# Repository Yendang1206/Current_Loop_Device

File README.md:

# Digital Current Loop Device for Frequency Converters
This repository contains the design and implementation details of a digital current loop device for frequency converters, developed as part of a thesis project. This device serves as an intermediate unit between a motor and a frequency converter, featuring advanced functionalities such as fast and slow increments or decrements for user-friendly control.
## Overview
The digital current loop device converts digital inputs—representing torque (0–50 Nm) and speed (0–3000 rpm)—into 0–20 mA analog current loops. This project integrates hardware and software to achieve precise control, accurate signal processing, and robust performance in noisy environments.
## Key Features
+ Converts torque and speed inputs from a rotary encoder into 0–20 mA current loop outputs.
+ Displays real-time input values on an LCD I2C screen.
+ Offers convenient fast/slow increment and decrement control.
+ Incorporates grounding, shielding, and paired signal wiring to enhance signal stability.
## The work methods
The work methods for this project were split into three main stages: 
 + circuit design, simulation and prototyping,
 + developing an Arduino software program,
 + manufacturing the physical Printed Circuit Boards (PCB).
## Results
Demonstrated positive correlation between torque and speed inputs with the corresponding current loop values (0–20 mA).
Achieved consistent performance between breadboard prototypes and integrated PCB systems.
Eliminated capacitive crosstalk and frequency interference using proper grounding, shielding, and CAT6 cable pairing.
## How to use
1. Connect the device between the motor and the frequency converter.
2. Adjust torque and speed inputs using the rotary encoder.
3. Monitor real-time input values on the LCD I2C display.
4. Verify current loop outputs using multimeters for accuracy.
## Future recommendations
Conduct EMC testing to further enhance noise immunity and long-term stability.

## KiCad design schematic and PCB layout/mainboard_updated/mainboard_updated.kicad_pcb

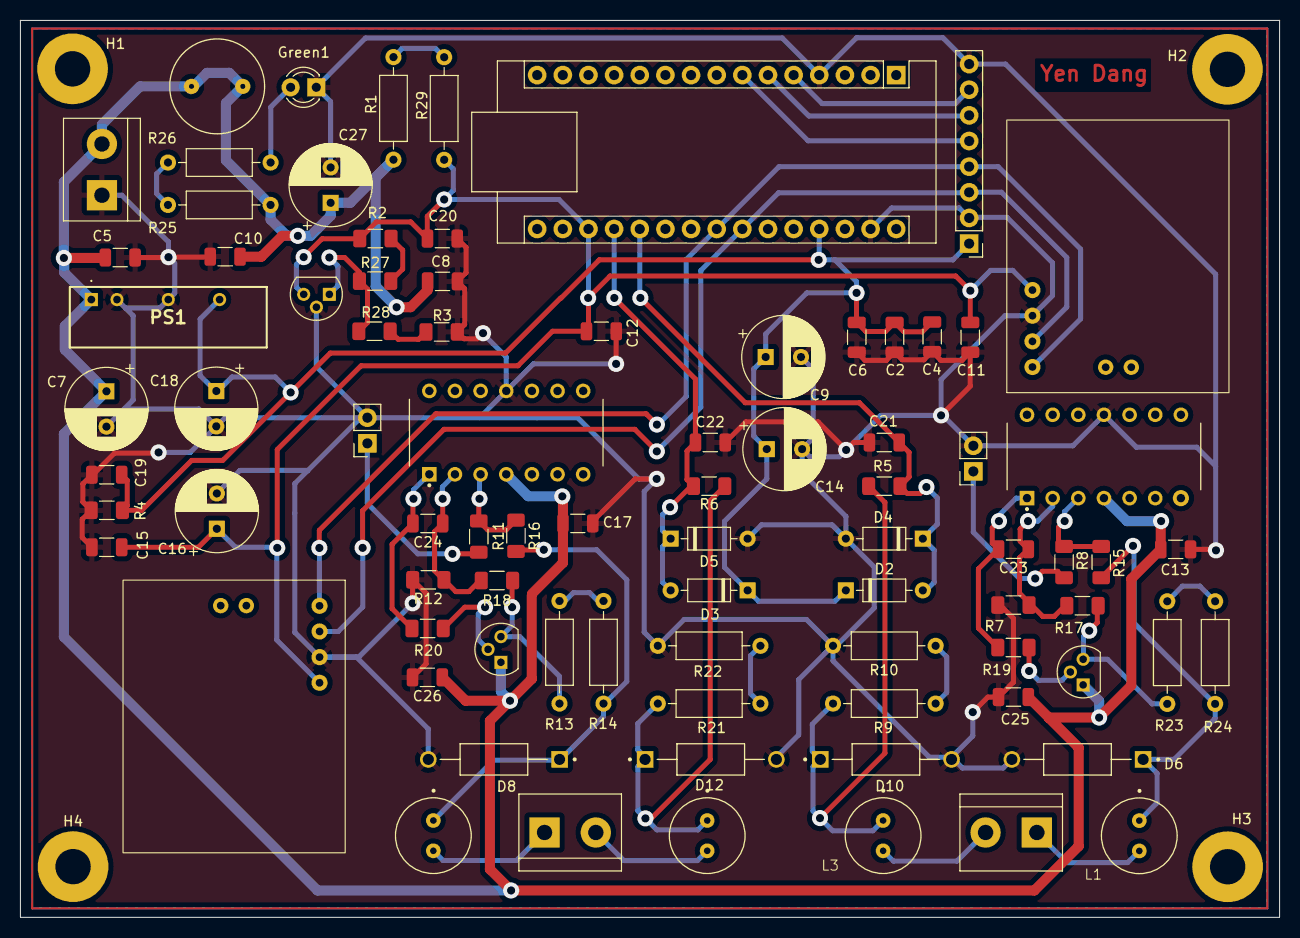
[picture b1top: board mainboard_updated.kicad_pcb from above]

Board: 2 copper layers, 124.7 x 88.8 mm, 87 parts (0 on the bottom side), 41 nets.

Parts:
 Green1: GreenLED; LED
A1: Arduino_Nano_v3.x; Arduino_Nano
BC547_1, BC547_2: BC547_TO92_0.1A; TO-92
C2, C4, C5, C6, C8, C10, C11, C12, C13, C15, C17, C19, C20, C21, C22, C23, C24, C25, C26: 100NF_50V_CER; C1206
C7, C9, C14, C16, C18, C27: 100UF_50V_ELE; C_P_3_5_8
D2, D3, D4, D5: 1N4148; D_DO-35_SOD27_P7.62mm_Horizontal
D6, D8, D10, D12: P6KE43CA; DIOAD1300W80L670D310
F1: TR5; FUSE_TR5
H1, H2, H3, H4: MountingHole_Pad_MP; MountingHole_3.5mm_Pad
L1, L2, L3, L4: Coil3; Coil3_100uH
PS1: AM2D-2405SZ; AM2D2405SZ
R1, R29: 910R; R3_5W
R2, R3, R5, R6: 10k; 1206
R4: 470R; 1206
R7, R8, R11, R12, R15, R16, R17, R18: 150k; 1206
R9, R13, R21, R23: 100R; R3_5W
R10, R14, R22, R24: 150R; R3_5W
R19, R20: 100R; 1206
R25, R26: 2.2k; R3_5W
R27: 0R; 1206
R28: 150R; 1206
ROW_VERT/1X1: ROW_VERT_1X8; ROW_VERT_1x8
SOCKET/1X1, SOCKET/1X2: SOCKET_1X2; SOCKET_1x2
TL431CLP1: TL431CLP_TO92; TO-92
TM_BLOCK/2P1, TM_BLOCK/2P2, TM_BLOCK/2P3: TM_BLOCK_2P
U1, U2: DFR0552
U3, U4: LM324NE4; DIP825W47P254L1917H533Q14

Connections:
5V: A1.27 (+5V), C2.1, C4.1, C6.1, C9.1, C14.1, C18.1, C19.1, D2.1 (K), D3.1 (K), PS1.6 (+V_OUT), R4.2, ROW_VERT/1X1.1
+24V: BC547_1.1 (C), BC547_2.1 (C), C5.1, C7.1, C8.1, C10.1, C13.1, C17.1, C25.1, C26.1, C27.1, F1.1, F1.2, PS1.1 (+Vin), R1.1, R25.2, TM_BLOCK/2P1.2, U3.4, U4.4
A0: A1.19 (A0), C22.1, D3.2 (A), D5.1 (K), R6.2
A1: A1.20 (A1), C21.1, D2.2 (A), D4.1 (K), R5.2
EncoderA: A1.5 (D2), ROW_VERT/1X1.7
EncoderB: A1.6 (D3), ROW_VERT/1X1.6
GND: Green1.1 (K), A1.4 (GND), A1.29 (GND), C2.2, C4.2, C5.2, C6.2, C7.2, C8.2, C9.2, C10.2, C11.1, C12.2, C13.2, C14.2, C15.1, C16.2, C17.2, C18.2, C19.2, C20.2, C21.2, C22.2, C25.2, C26.2, C27.2, D4.2 (A), D5.2 (A), D6.A, D8.A, D10.A, D12.A, PS1.2 (-Vin), PS1.4 (-V_OUT), R3.1, R4.1, R7.1, R10.1, R12.1, R22.1, ROW_VERT/1X1.2, ROW_VERT/1X1.8, SOCKET/1X1.2, SOCKET/1X2.2, TL431CLP1.2 (A), TM_BLOCK/2P1.1, U1.2 (GND), U2.2 (GND), U3.11, U4.11
unnamed: Green1.2 (A), R26.1
unnamed: BC547_1.2 (B), R19.2
unnamed: BC547_1.3 (E), R17.2, R23.2
unnamed: BC547_2.2 (B), R20.2
unnamed: BC547_2.3 (E), R13.2, R18.2
unnamed: C23.1, R7.2, R17.1, U3.2
unnamed: C23.2, R19.1, U3.1
unnamed: C24.1, R12.2, R18.1, U4.2
unnamed: C24.2, R20.1, U4.1
unnamed: D6.C, L1.1, R15.1, R24.1
unnamed: D8.C, L2.1, R14.1, R16.1
unnamed: D10.C, L3.1, R5.1, R9.2
unnamed: D12.C, L4.1, R6.1, R21.2
unnamed: R1.2, R29.1
unnamed: R2.1, R27.2
unnamed: R9.1, R10.2
unnamed: R11.2, R16.2, U4.3
unnamed: R13.1, R14.2
unnamed: R8.2, R15.2, U3.3
unnamed: R21.1, R22.2
unnamed: R23.1, R24.2
unnamed: R25.1, R26.2
unnamed: R3.2, R28.1
unnamed: R27.1, R28.2, TL431CLP1.1 (REF)
unnamed: L1.2, TM_BLOCK/2P2.1
unnamed: L3.2, TM_BLOCK/2P2.2
unnamed: L2.2, TM_BLOCK/2P3.1
unnamed: L4.2, TM_BLOCK/2P3.2
SCL: A1.24 (A5), ROW_VERT/1X1.3, U1.3 (SCL), U2.3 (SCL)
SDA: A1.23 (A4), ROW_VERT/1X1.4, U1.4 (SDA), U2.4 (SDA)
SW1: A1.7 (D4), ROW_VERT/1X1.5
V_DAC1: R8.1, SOCKET/1X1.1
V_DAC2: R11.1, SOCKET/1X2.1
Vref: A1.18 (AREF), C11.2, C12.1, C15.2, C16.1, C20.1, R2.2, R29.2, TL431CLP1.3 (K), U1.1 (VCC), U2.1 (VCC)

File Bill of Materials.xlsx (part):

|  | Bill of Materials |  |  |  |  |  |  | Note
Supplier | No. | Description | Order Code | Quantity | Unit Price (incl. VAT) (EUR) | Price (incl. VAT) (EUR) |  |  | Reference | Supplier
Elfa | 1 | Capacitor 100NF_50V_CER | 165-77-688 | 23 | 0.37469999999999998 | 8.6181000000000001 |  |  | C1-C6, C8, C10-C13, C15, C17, C19-C26,C6, C8, C10, C12 | https://www.elfadistrelec.fi/fi/keraaminen-kondensaattori-10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
Elfa | 2 | Capacitor 100UF_50V_ELE | 300-92-030 | 7 | 0.18720000000000001 | 1.3104 |  |  | C7, C9, C14, C16, C18, C3, C27 | https://www.elfadistrelec.fi/fi/radiaalinen-elektrolyyttikon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
Elfa | 3 | ROW_VERT_1X8 | 43-70-219 | 1 | 1.18 | 1.18 |  |  | ROW_VERT/1X1, ROW_VERT/1X2 | https://www.elfadistrelec.fi/fi/piikkirima-uros-1a-kontaktie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
Elfa | 4 | LCD holder for the small metal box | 175-57-723 | 1 | 21.06 | 21.06 |  |  | LCD holder for the small metal box | https://www.elfadistrelec.fi/fi/lcd-naeytoen-etukehys-displa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
Elfa | 5 | Cable CAT6 1.5m | 302-29-454 | 1 | 5.99 | 5.99 |  |  | Cable CAT 6 1.5m | https://www.elfadistrelec.fi/fi/kytkentaekaapeli-rj45-urosli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
Elfa | 6 | EMC sleeve seal | 301-40-348 | 5 | 8.7100000000000009 | 43.550000000000004 |  |  | EMC sleeve seal | https://www.elfadistrelec.fi/fi/emc-holkkitiiviste-10mm-m16-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
Farnell | 7 | GreenLED | 3796272 | 1 | 0.28148000000000001 | 0.28148000000000001 |  |  | Green1 | https://fi.farnell.com/en-FI/multicomp-pro/mp008246/led-gree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
Farnell | 8 | Arduino_Nano_v3.x | 1848691 | 1 | 26.077200000000001 | 26.077200000000001 |  |  | A1 | https://fi.farnell.com/arduino/a000005/arduino-nano-evaluati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
Farnell | 9 | BC547_TO92_0.1A | 1017673 | 2 | 0.155 | 0.31 |  |  | BC547_1, BC547_2 | https://fi.farnell.com/en-FI/onsemi/bc547bg/transistor-npn-4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
Farnell | 10 | 1N4148 | 9843680 | 4 | 1.9096000000000002E-2 | 7.6384000000000007E-2 |  |  | D2-D5 | https://fi.farnell.com/en-FI/multicomp-pro/1n4148/diode-ultr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
Farnell | 11 | P6KE43CA/P6KEG39CA | 3226355 | 5 | 0.33604000000000001 | 1.6802000000000001 |  |  | D6-D13,D1 | https://fi.farnell.com/en-FI/multicomp-pro/p6keg39ca/tvs-dio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
Farnell | 12 | Resistor 1.8k SMD (replace by 2 TH resistors of 910R) | Removed |  |  | 0 |  |  |  | https://fi.farnell.com/en-FI/panasonic/era8aeb182v/res-1k8-0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
Farnell | 13 | Resistor 10k SMD (update footprint from 2010 to 1206) | 1469655 | 12 | 0.42160000000000003 | 5.0592000000000006 |  |  | R2, R3, R5, R6, R1-R8 | https://fi.farnell.com/en-FI/vishay/crcw120610k0jnea/res-10k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
Farnell | 14 | Resistor 470R SMD (update footprint from 0805 to 1206) | 2671182 | 1 | 2.3311999999999999E-2 | 2.3311999999999999E-2 |  |  | R4 | https://fi.farnell.com/en-FI/walsin/wr12x471-jtl/res-470r-5-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
Farnell | 15 | Resistor 150k SMD | 1841797 | 8 | 0.36207999999999996 | 2.8966399999999997 |  |  | R7, R8, R11, R12, R15-R18 | https://fi.farnell.com/en-FI/panasonic/era8aeb154v/res-150k-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
Farnell | 16 | Resistor 100R SMD | 3392888 | 2 | 5.0963999999999995E-2 | 0.10192799999999999 |  |  | R19, R20 | https://fi.farnell.com/en-FI/multicomp-pro/mp003694/res-100r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
Farnell | 17 | Resistor 100R TH (change from 400mW to 600mW) | 9463909 | 4 | 0.18103999999999998 | 0.72415999999999991 |  |  | R9, R13, R21, R23 | https://fi.farnell.com/vishay/mrs25000c1000fct00/res-100r-1-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
Farnell | 18 | Resistor 150R TH (change from 250mW to 600mW) | 9464638 | 4 | 0.17731999999999998 | 0.70927999999999991 |  |  | R10, R14, R22, R24 | https://fi.farnell.com/vishay/mrs25000c1500fct00/res-150r-1-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
Farnell | 19 | Resistor 2.2k TH (change from 2W to 600mW) | 9466711 | 2 | 0.18103999999999998 | 0.36207999999999996 |  |  | R25, R26 | https://fi.farnell.com/vishay/mrs25000c2201fct00/res-2k2-1-6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
Farnell | 20 | SOCKET_1X8 (replace for ROW_VERTICAL HEADER at mainboard) | 2802333 | 1 | 1.08128 | 1.08128 |  |  | Replace for ROW_VERTICAL PIN HEADER at mainboard | https://fi.farnell.com/en-FI/mcm/83-15410/1-x-8-position-fem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
Farnell | 21 | SOCKET*2_1X10 | 1593464 | 1 | 0.52700000000000002 | 0.52700000000000002 |  |  | SOCKET/1X1, SOCKET/1X2 | https://fi.farnell.com/multicomp/2212s-10sg-85/socket-pcb-1-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
Farnell | 22 | TL431CLP_TO92 | 9756450 | 1 | 0.87791999999999992 | 0.87791999999999992 |  |  | TL431CLP1 | https://fi.farnell.com/stmicroelectronics/tl431acz/voltage-r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
Farnell | 23 | TM_BLOCK_2P | 3882652 | 4 | 2.3559999999999999 | 9.4239999999999995 |  |  | TM_BLOCK/2P1-TM_BLOCK/2P3 | https://fi.farnell.com/camdenboss/ctb0308-2/terminal-block-w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
Farnell | 24 | DFR0552 | 3517945 | 2 | 6.2247999999999992 | 12.449599999999998 |  |  | U1, U2 | https://fi.farnell.com/dfrobot/dfr0552/i2c-12-bit-dac-module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
Farnell | 25 | Capacitor 10NF_50V_CER SMD (update footprint from 0402 to 1206) | 2906003 | 3 | 0.13267999999999999 | 0.39803999999999995 |  |  | C1, C2, C4 | https://fi.farnell.com/kemet/c0402c103j5racauto/cap-0-01-f-5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
Farnell | 26 | ROW_VERT_1X4 | 2852586 | 1 | 0.2666 | 0.2666 |  |  | ROW_VERT/1X1 | https://fi.farnell.com/en-FI/multicomp/mc-hvt1-s04-g/connect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
Farnell | 27 | TVS Varistor | 1004301 | 1 | 1.1160000000000001 | 1.1160000000000001 |  |  | RV1 | https://fi.farnell.com/epcos/b72220s0500k101/varistor-27-0j-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
Farnell | 28 | Filter B82725S2103N003 | 3580935 | 1 | 11.209599999999998 | 11.209599999999998 |  |  | FL1 | https://fi.farnell.com/epcos/b82725s2103n003/power-line-chok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
Farnell | 29 | Toroidal Inductor, Vertical, 100uH | 2215971 | 1 | 6.6464000000000008 | 6.6464000000000008 |  |  | L1 | https://fi.farnell.com/pulse-electronics/pe-92112knl/inducto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
Farnell | 30 | Capacitor 10nF TH | 2576736 | 1 | 0.34720000000000001 | 0.34720000000000001 |  |  | C2 (filter circuit) | https://fi.farnell.com/walsin/yv1ac103m140d20c7b/cap-0-01-f-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
Farnell | 31 | Capacitor 2200pF TH | 2507755 | 2 | 0.59519999999999995 | 1.1903999999999999 |  |  | C1 and C3 (filter circuit) | https://fi.farnell.com/vishay/vy1222m47y5uq6uv0/cap-2200pf-2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
Farnell | 32 | Encoder's knob | Removed |  |  | 0 |  |  | Encoder's knob | https://fi.farnell.com/alcoswitch-te-connectivity/pka50b1-4/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
Farnell | 33 | Screw 3.5x12mm | 2400762 | 12 | 2.3188 | 27.825600000000001 |  |  | Screw 3.5x12mm | https://fi.farnell.com/deltron-components/000-035-004/std-sc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
Farnell | 34 | Heat Sink, 60 °C/W, TO-92, 15.29 mm, 18.29 mm | 2822615 | 2 | 6.2619999999999996 | 12.523999999999999 |  |  | Heatsink for TO-92 transistor | https://fi.farnell.com/en-FI/aavid-thermalloy/575200b00000g/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
Farnell | 35 | Resistor 910R TH | 9470581 | 2 | 0.1736 | 0.34720000000000001 |  |  | R1, R29 | https://fi.farnell.com/en-FI/vishay/mrs25000c9100fct00/res-9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
Farnell | 36 | Resistor 0R SMD | 9240276 | 1 | 3.7199999999999997E-2 | 3.7199999999999997E-2 |  |  | R27 | https://fi.farnell.com/en-FI/yageo/rc1206jr-070rl/res-0r0-5-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
Farnell | 37 | Resistor 150R SMD | 2531869 | 1 | 0.23808000000000001 | 0.23808000000000001 |  |  | R28 | https://fi.farnell.com/en-FI/te-connectivity/crgs1206j150r/r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
Farnell | 38 | TM_BLOCK_3P | 3882664 | 1 | 3.4471999999999996 | 3.4471999999999996 |  |  | TM_BLOCK_3P (filter circuit) | https://fi.farnell.com/camdenboss/ctb0308-3/terminal-block-w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
Partco | 39 | LCD I2C | LCD 2X16-I2C | 1 | 12.8 | 12.8 |  |  | LCD I2C | https://www.partco.fi/fi/naeytoet/lcd-naeytoet/20158-lcd-2x1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
Partco | 40 | Heatsinks for power chip (2pcs/1bag) | RPI-02893 | 1 | 4.8 | 4.8 |  |  | Heatsinks for power chip | https://www.partco.fi/fi/laemmoenhallinta/jaeaehdytyselement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
Starelec | 41 | TR5-K | 170-00181 | 1 | 0.55000000000000004 | 0.55000000000000004 |  |  | F1 | https://www.starelec.fi/product_info.php?cPath=66_335_3295&p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
Starelec | 42 | COIL3-100UH (mainboard) | COIL3-100UH | 4 | 0.5 | 2 |  |  | L1-L4 | https://www.starelec.fi/product_info.php?products_id=21043
Starelec | 43 | AM2D-2405SZ | DC2WS-2405S | 1 | 7.06 | 7.06 |  |  | PS1 | https://www.starelec.fi/product_info.php?cPath=72_155_2374&p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
Starelec | 44 | LM324NE4 | LM324N | 2 | 0.74 | 1.48 |  |  | U3, U4 | https://www.starelec.fi/product_info.php?products_id=112
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
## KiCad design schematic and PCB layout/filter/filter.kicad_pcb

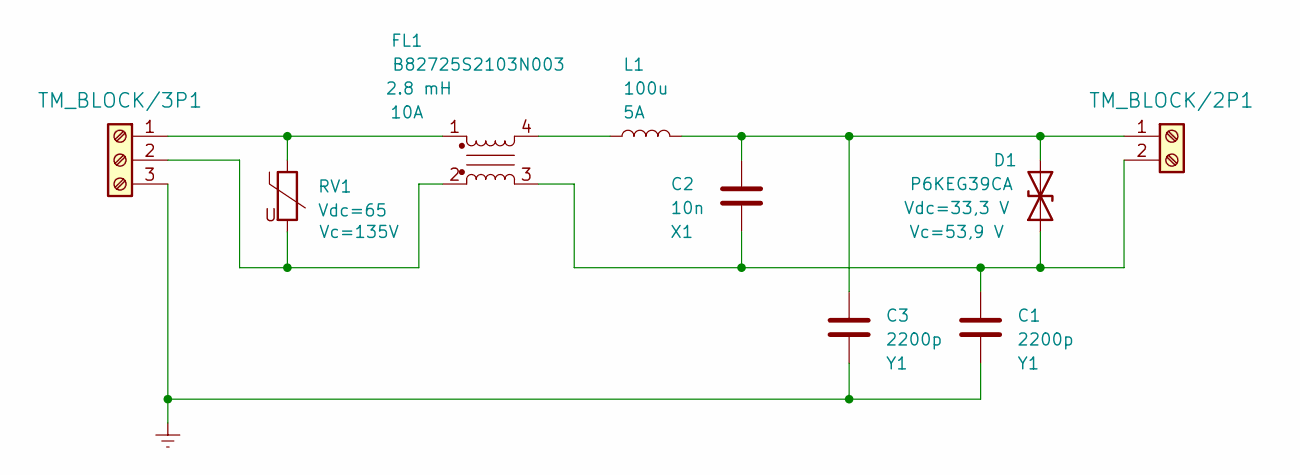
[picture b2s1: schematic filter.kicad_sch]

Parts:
C1, C3: 2200p; CAP_DE2E3SA222MJ3BT02F; Farnell 2507755
C2: 10n; CAPRB250W50L450T300H550; Farnell 2576736
D1: P6KEG39CA; DIOAD1995W86L635D340; Farnell 3226355
FL1: 2.8 mH; B82725S2103N003; Farnell 3580935
L1: 100u; PE92112KNL; Farnell 2215971
RV1: Vdc=65; B72220S0500K101; Farnell 1004301
TM_BLOCK/2P1: TM_BLOCK_2P
TM_BLOCK/3P1: TM_BLOCK_3P

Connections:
GNDREF: C1.2, C3.2, TM_BLOCK/3P1.3
unnamed: C1.1, C2.2, D1.1 (A1), FL1.3, TM_BLOCK/2P1.2
unnamed: C2.1, C3.1, D1.2 (A2), L1.2, TM_BLOCK/2P1.1
unnamed: FL1.4, L1.1
unnamed: FL1.1, RV1.1, TM_BLOCK/3P1.1
unnamed: FL1.2, RV1.2, TM_BLOCK/3P1.2

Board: 2 copper layers, 9 parts (0 on the bottom side), 6 nets, no tracks yet.

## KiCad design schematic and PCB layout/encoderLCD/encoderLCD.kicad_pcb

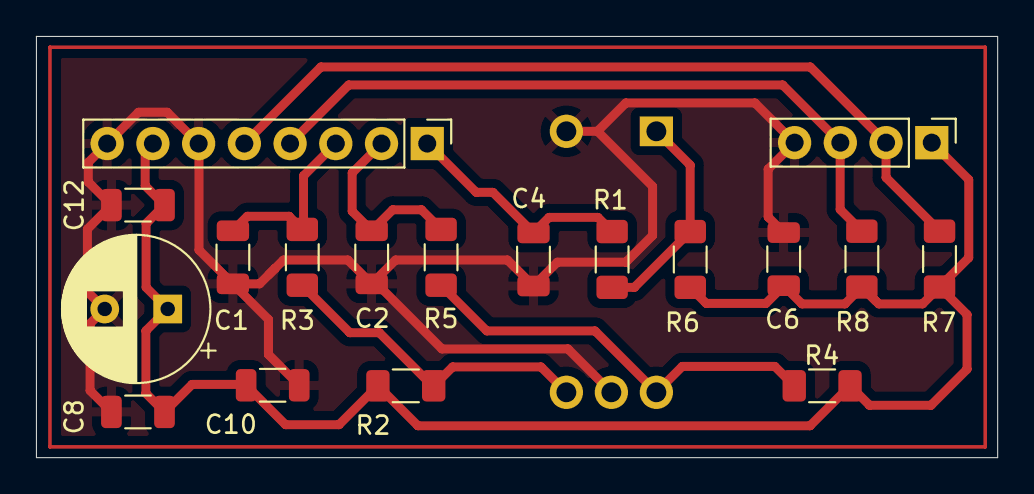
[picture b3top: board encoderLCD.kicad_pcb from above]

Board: 2 copper layers, 53.4 x 23.4 mm, 19 parts (1 on the bottom side), 10 nets.

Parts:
C1, C2, C4: 10NF_50V_CER; C1206
C3: 100UF_50V_ELE; C_P_3_5_8
C6, C8, C10, C12: 100NF_50V_CER; C1206
R1, R2, R3, R4, R5, R6, R7, R8: 10k; 1206
ROW_VERT/1X1: ROW_VERT_1X4; ROW_VERT_1x4
ROW_VERT/1X2: ROW_VERT_1X8; ROW_VERT_1x8
SW1: Encoder; XDCR_PEC11R-4215F-S0024

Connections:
5V: C3.1, C6.1, C8.1, C10.1, C12.1, R2.1, R4.2, R6.1, R7.1, R8.1, ROW_VERT/1X1.1, ROW_VERT/1X2.7
EncoderA: C2.1, R5.2, ROW_VERT/1X2.2
EncoderB: C1.1, R3.2, ROW_VERT/1X2.3
GND: C1.2, C2.2, C3.2, C4.2, C6.2, C8.2, C10.2, C12.2, ROW_VERT/1X1.4, ROW_VERT/1X2.6, ROW_VERT/1X2.8, SW1.COM, SW1.S2
unnamed: R1.1, R6.2, SW1.S1
unnamed: R2.2, R3.1, SW1.B
unnamed: R4.1, R5.1, SW1.A
SCL: R8.2, ROW_VERT/1X1.3, ROW_VERT/1X2.4
SDA: R7.2, ROW_VERT/1X1.2, ROW_VERT/1X2.5
SW1: C4.1, R1.2, ROW_VERT/1X2.1

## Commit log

2024-10-14 add all project files
2024-12-19 add simulation and final report
